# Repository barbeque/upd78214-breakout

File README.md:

This is an in-progress project. None of it is likely to work.

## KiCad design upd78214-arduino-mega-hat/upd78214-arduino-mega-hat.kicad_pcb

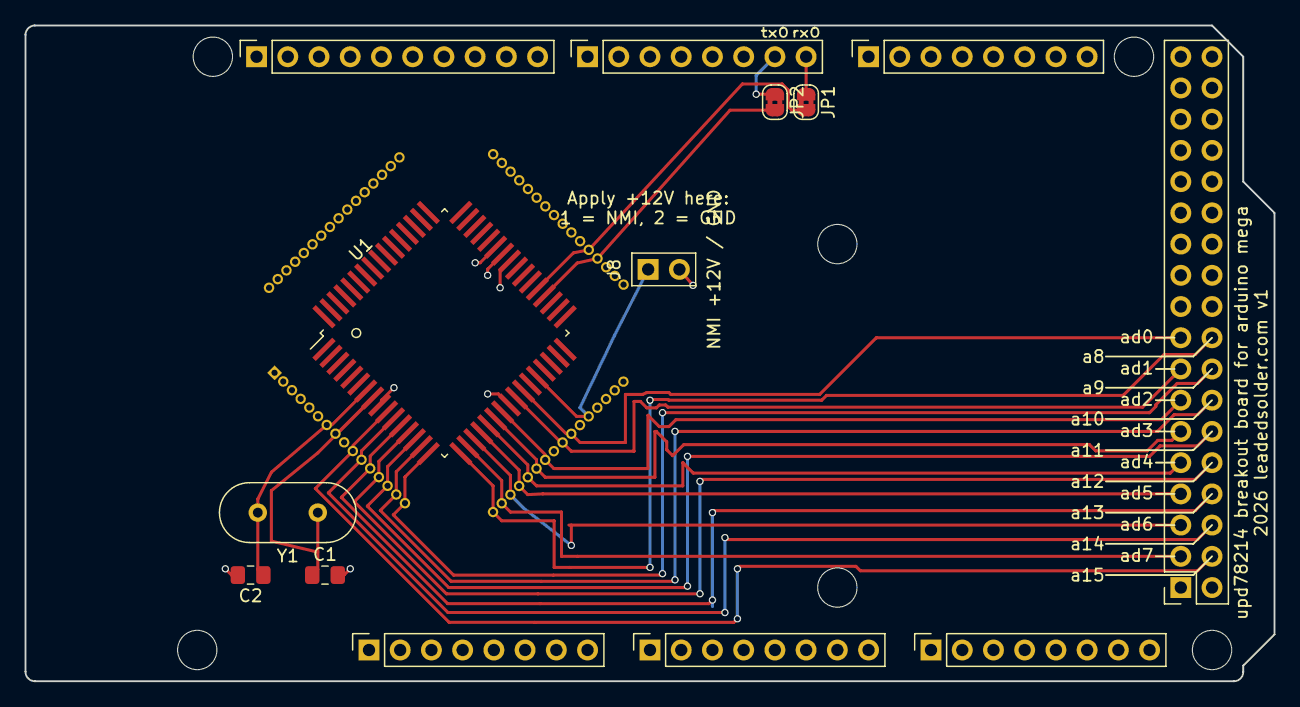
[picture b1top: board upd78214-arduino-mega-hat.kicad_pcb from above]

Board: 4 copper layers, 101.6 x 53.3 mm, 20 parts (0 on the bottom side), 27 nets.

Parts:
C1, C2: 30pF; C_0805_2012Metric_Pad1.18x1.45mm_HandSolder
J1: Power; PinSocket_1x08_P2.54mm_Vertical
J2: PWM; PinSocket_1x10_P2.54mm_Vertical
J3, J5: Analog; PinSocket_1x08_P2.54mm_Vertical
J4: PWM; PinSocket_1x08_P2.54mm_Vertical
J6: Communication; PinSocket_1x08_P2.54mm_Vertical
J7: Digital; PinSocket_2x18_P2.54mm_Vertical
J8: NMI +12V / GND; PinHeader_1x02_P2.54mm_Vertical
JP1, JP2: Jumper_2_Bridged; SolderJumper-2_P1.3mm_Bridged2Bar_RoundedPad1.0x1.5mm
MH1, MH2, MH3, MH4, MH5, MH6: MountingHole_3.2mm
U1: upd78214-64p-qfp; QFP-64_14x14_Pitch0.8mm
Y1: 4-12MHz; Crystal_HC49-U_Vertical

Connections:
+5V: J1.5, J7.35, J7.36, U1.41 (Vdd), U1.43 (AVref)
/NMI: J8.1, U1.28 (p2,0/nmi)
/RX0/0: J4.8, JP1.1 (A)
/SCL/21: J2.1, J6.8
/SDA/20: J2.2, J6.7
/TX0/1: J4.7, JP2.1 (A)
/a8: J7.18, U1.17 (p5,0/a8)
/a9: J7.16, U1.16 (p5,1/a9)
/a10: J7.14, U1.15 (p5,2/a10)
/a11: J7.12, U1.14 (p5,3/a11)
/a12: J7.10, U1.13 (p5,4/a12)
/a13: J7.8, U1.12 (p5,5/a13)
/a14: J7.6, U1.11 (p5,6/a14)
/a15: J7.4, U1.10 (p5,7/a15)
/ad0: J7.17, U1.26 (p4,0/ad0)
/ad1: J7.15, U1.25 (p4,1/ad1)
/ad2: J7.13, U1.23 (p4,2/ad2)
/ad3: J7.11, U1.22 (p4,3/ad3)
/ad4: J7.9, U1.21 (p4,4/ad4)
/ad5: J7.7, U1.20 (p4,5/ad5)
/ad6: J7.5, U1.19 (p4,6/ad6)
/ad7: J7.3, U1.18 (p4,7/ad7)
GND: C1.2, C2.2, J1.6, J1.7, J2.4, J7.1, J7.2, J8.2, U1.9 (Vss), U1.24 (Vss), U1.42 (AVss)
unnamed: JP1.2 (B), U1.37 (p3,1/txd)
unnamed: JP2.2 (B), U1.36 (p3,0/rxd)
unnamed: C1.1, U1.8 (X1), Y1.1
unnamed: C2.1, U1.7 (X2), Y1.2

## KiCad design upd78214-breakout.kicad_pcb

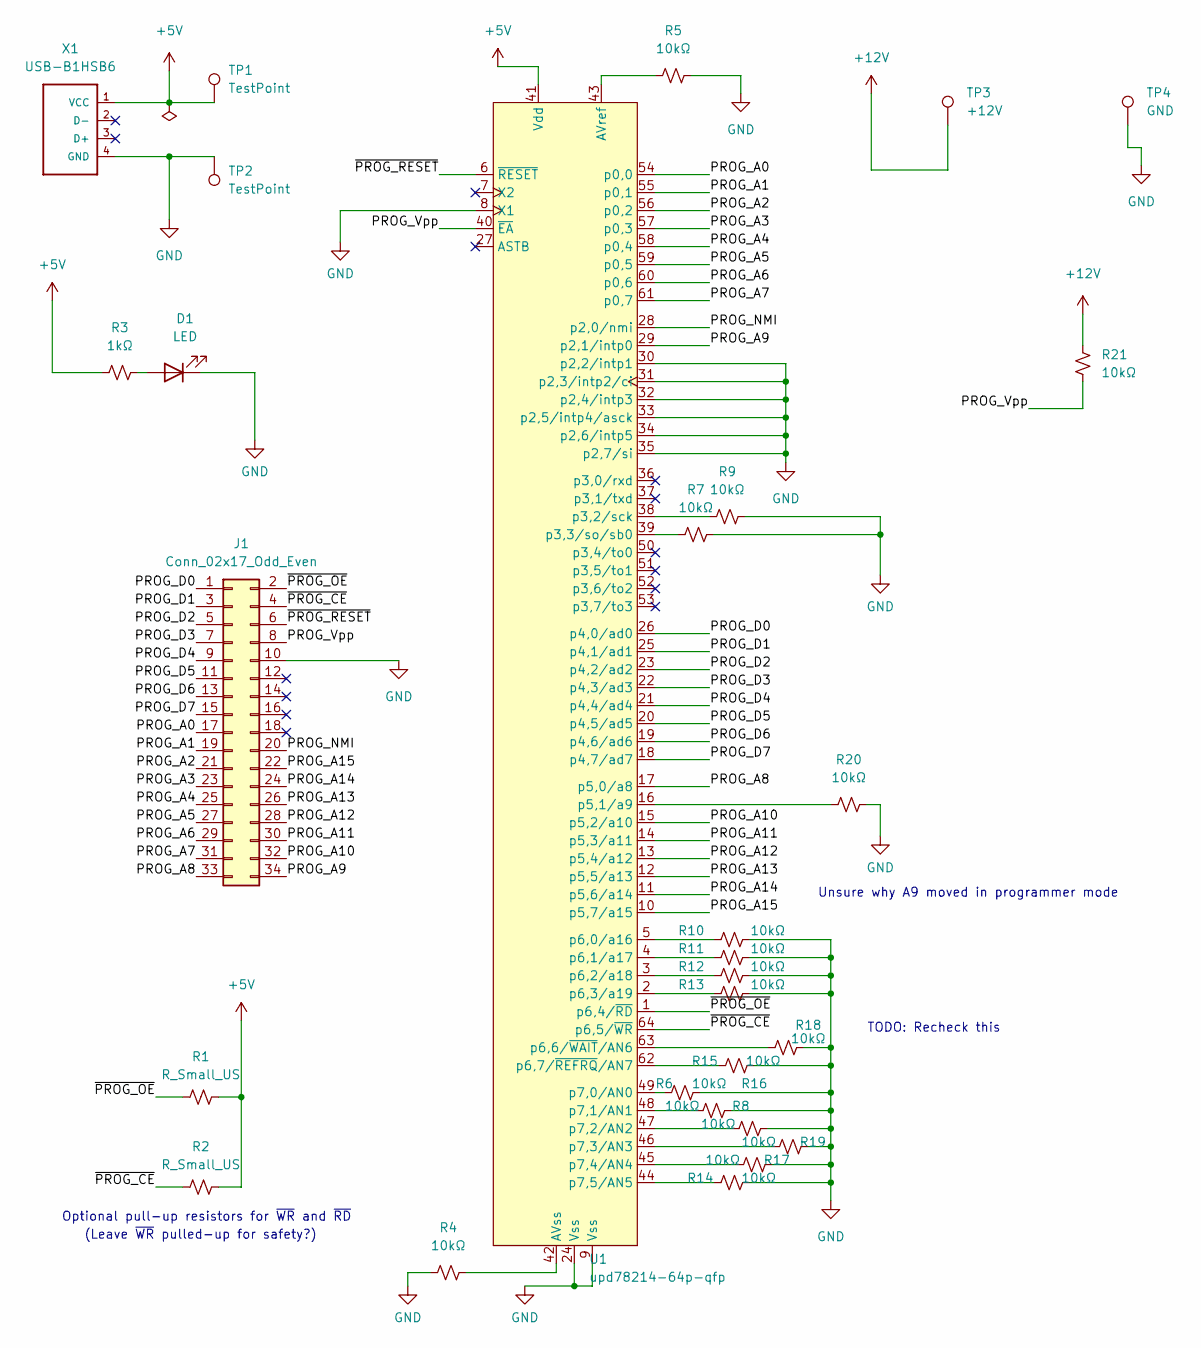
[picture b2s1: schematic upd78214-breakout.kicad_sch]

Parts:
D1: LED; LED_D3.0mm
J1: Conn_02x17_Odd_Even; PinSocket_2x17_P2.54mm_Vertical
R1, R2: R_Small_US; R_Axial_DIN0207_L6.3mm_D2.5mm_P10.16mm_Horizontal
R3: 1kΩ; R_Axial_DIN0207_L6.3mm_D2.5mm_P10.16mm_Horizontal
R4, R5, R6, R7, R8, R9, R10, R11, R12, R13, R14, R15, R16, R17, R18, R19, R20, R21: 10kΩ; R_Axial_DIN0207_L6.3mm_D2.5mm_P10.16mm_Horizontal
TP1, TP2: TestPoint; TestPoint_Loop_D2.50mm_Drill1.0mm
TP3: +12V; TestPoint_Bridge_Pitch5.08mm_Drill0.7mm
TP4: GND; TestPoint_Bridge_Pitch5.08mm_Drill0.7mm
U1: upd78214-64p-qfp; QFP-64_14x14_Pitch0.8mm
X1: USB-B1HSB6; OST_USB-B1HSB6; DigiKey ED2983-ND

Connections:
+5V: R1.2, R2.2, R3.1, TP1.1, U1.41 (Vdd), X1.1 (VCC); also elsewhere on the board
+12V: R21.1, TP3.1
/PROG_A0: J1.17, U1.54 (p0,0)
/PROG_A1: J1.19, U1.55 (p0,1)
/PROG_A2: J1.21, U1.56 (p0,2)
/PROG_A3: J1.23, U1.57 (p0,3)
/PROG_A4: J1.25, U1.58 (p0,4)
/PROG_A5: J1.27, U1.59 (p0,5)
/PROG_A6: J1.29, U1.60 (p0,6)
/PROG_A7: J1.31, U1.61 (p0,7)
/PROG_A8: J1.33, U1.17 (p5,0/a8)
/PROG_A9: J1.34, U1.29 (p2,1/intp0)
/PROG_A10: J1.32, U1.15 (p5,2/a10)
/PROG_A11: J1.30, U1.14 (p5,3/a11)
/PROG_A12: J1.28, U1.13 (p5,4/a12)
/PROG_A13: J1.26, U1.12 (p5,5/a13)
/PROG_A14: J1.24, U1.11 (p5,6/a14)
/PROG_A15: J1.22, U1.10 (p5,7/a15)
/PROG_D0: J1.1, U1.26 (p4,0/ad0)
/PROG_D1: J1.3, U1.25 (p4,1/ad1)
/PROG_D2: J1.5, U1.23 (p4,2/ad2)
/PROG_D3: J1.7, U1.22 (p4,3/ad3)
/PROG_D4: J1.9, U1.21 (p4,4/ad4)
/PROG_D5: J1.11, U1.20 (p4,5/ad5)
/PROG_D6: J1.13, U1.19 (p4,6/ad6)
/PROG_D7: J1.15, U1.18 (p4,7/ad7)
/PROG_NMI: J1.20, U1.28 (p2,0/nmi)
/PROG_Vpp: J1.8, R21.2, U1.40 (~EA)
/~PROG_CE: J1.4, R2.1, U1.64 (p6,5/~WR)
/~PROG_OE: J1.2, R1.1, U1.1 (p6,4/~RD)
/~PROG_RESET: J1.6, U1.6 (~RESET)
GND: D1.1 (K), J1.10, R4.1, R5.2, R6.2, R7.2, R8.2, R9.2, R10.2, R11.2, R12.2, R13.2, R14.2, R15.2, R16.2, R17.2, R18.2, R19.2, R20.2, TP2.1, TP4.1, U1.8 (X1), U1.9 (Vss), U1.24 (Vss), U1.30 (p2,2/intp1), U1.31 (p2,3/intp2/ci), U1.32 (p2,4/intp3), U1.33 (p2,5/intp4/asck), U1.34 (p2,6/intp5), U1.35 (p2,7/si), X1.4 (GND); also elsewhere on the board
unnamed: D1.2 (A), R3.2
unnamed: R4.2, U1.42 (AVss)
unnamed: R5.1, U1.43 (AVref)
unnamed: R6.1, U1.49 (p7,0/AN0)
unnamed: R7.1, U1.39 (p3,3/so/sb0)
unnamed: R8.1, U1.48 (p7,1/AN1)
unnamed: R9.1, U1.38 (p3,2/sck)
unnamed: R10.1, U1.5 (p6,0/a16)
unnamed: R11.1, U1.4 (p6,1/a17)
unnamed: R12.1, U1.3 (p6,2/a18)
unnamed: R13.1, U1.2 (p6,3/a19)
unnamed: R14.1, U1.44 (p7,5/AN5)
unnamed: R15.1, U1.62 (p6,7/~REFRQ/AN7)
unnamed: R16.1, U1.47 (p7,2/AN2)
unnamed: R17.1, U1.45 (p7,4/AN4)
unnamed: R18.1, U1.63 (p6,6/~WAIT/AN6)
unnamed: R19.1, U1.46 (p7,3/AN3)
unnamed: R20.1, U1.16 (p5,1/a9)

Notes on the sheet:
Optional pull-up resistors for ~{WR} and ~{RD}
TODO: Recheck this
(Leave ~{WR} pulled-up for safety?)
Unsure why A9 moved in programmer mode

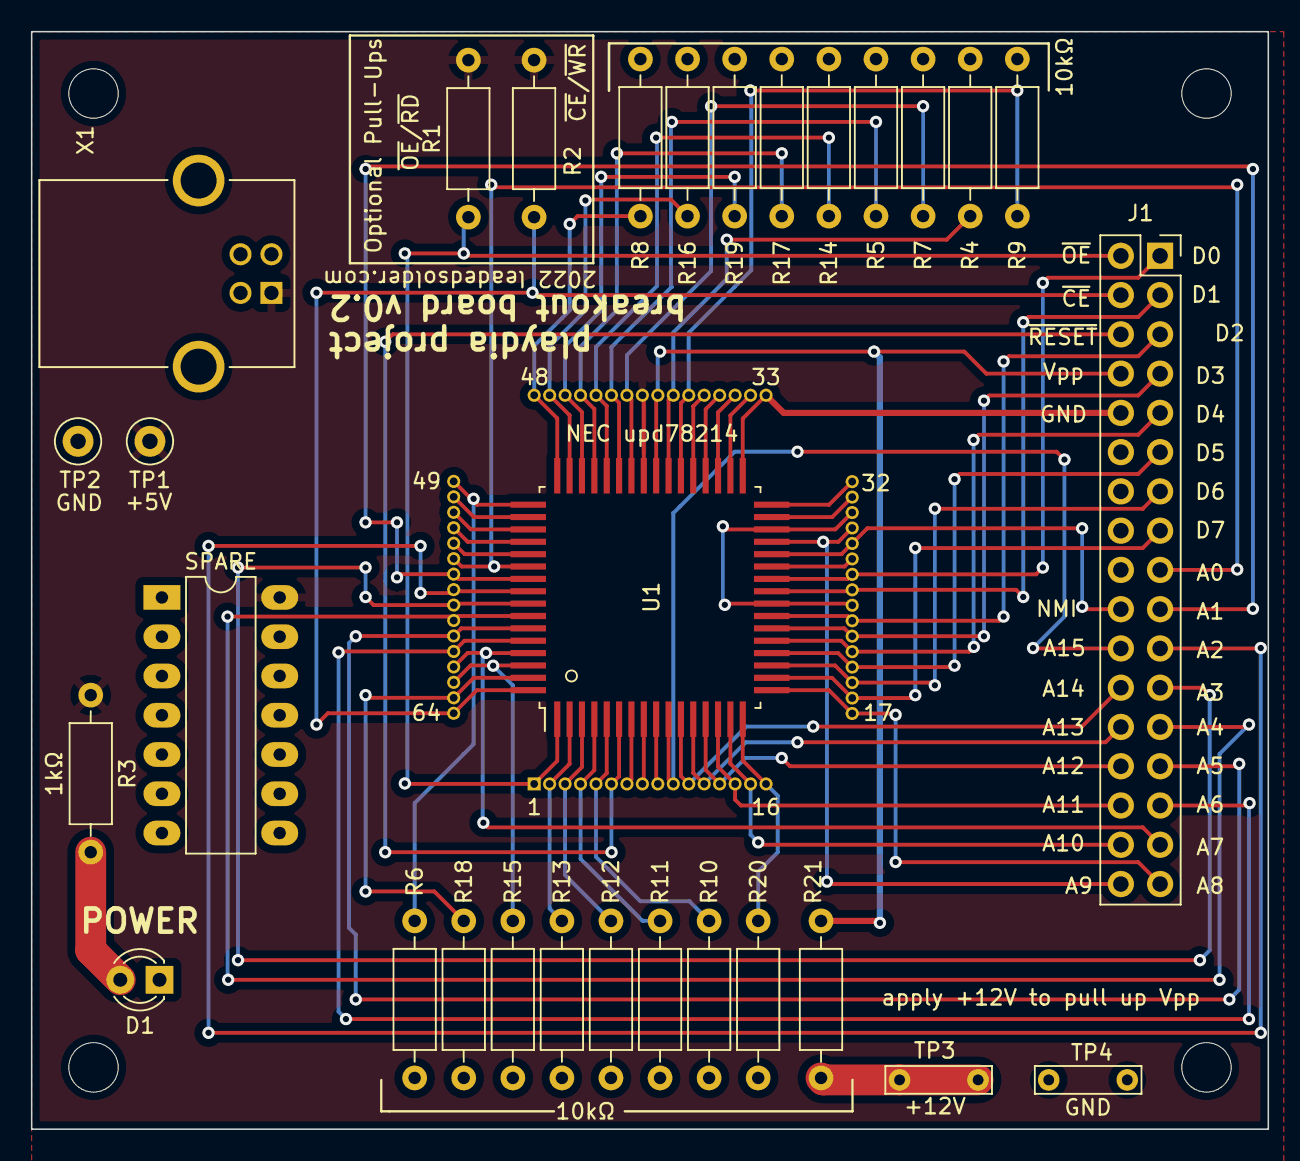
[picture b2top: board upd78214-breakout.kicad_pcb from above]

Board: 2 copper layers, 80.0 x 71.0 mm, 30 parts (0 on the bottom side), 50 nets.

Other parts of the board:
SPARE: DIP-14_W7.62mm_LongPads

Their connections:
+5V: SPARE.14; also elsewhere on the board
GND: SPARE.7; also elsewhere on the board

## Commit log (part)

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2022-09-18 Symbol done
2022-09-18 Ignore gitignore
2022-09-18 Fix VSS/VDD confusion
2022-09-21 NEC footprint, Toshiba symbol
2022-09-21 USB power for test board
2022-09-21 Fix 3d model
2022-09-21 Prog pins labelled
2022-09-23 Breakout pins for NEC
2022-09-24 Dumper V1 sent to Jonko
2022-09-24 Refresh info
2022-10-04 Break out NMI pin
2022-10-05 Re-route complete
2022-10-10 12V injection hooks
2022-10-10 V2 released
2026-03-30 Starting on HAT version
2026-03-30 Remove lock files
2026-03-30 Rambling
2026-03-30 TX/RX jumpers, enormous memory products data book
2026-03-30 Route a8..15
2026-03-30 Applying programming mode notes
2026-03-30 modes-table
2026-03-30 Warning
2026-03-30 Add pinouts
2026-03-30 Touch up modes table
2026-03-30 Fix markdown
2026-03-30 Notes on pins
